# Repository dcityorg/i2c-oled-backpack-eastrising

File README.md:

#### I²C OLED Backpack Board for the East Rising OLED display (2 rows by 16 characters)

<div style="text-align: center;">
<div style="display: inline-block; margin-right: 5px;">

</div>
<div style="display: inline-block; margin-right: 5px;">

</div>
<div style="display: inline-block; margin-right: 5px;">

</div>
</div>

Introduction
-------------------

**[This link has details](https://www.dcity.org/portfolio/i2c-oled-backpack-board-eastrising) including**
* parts lists
* assembly instructions
* jumper configuration
* Arduino, Particle and Raspberry Pi software library usage
* Bare PC boards are available from OSHPark.

**License Information**
Open Source Hardware Design. Our License Information is [here](https://www.dcity.org/license-information/).

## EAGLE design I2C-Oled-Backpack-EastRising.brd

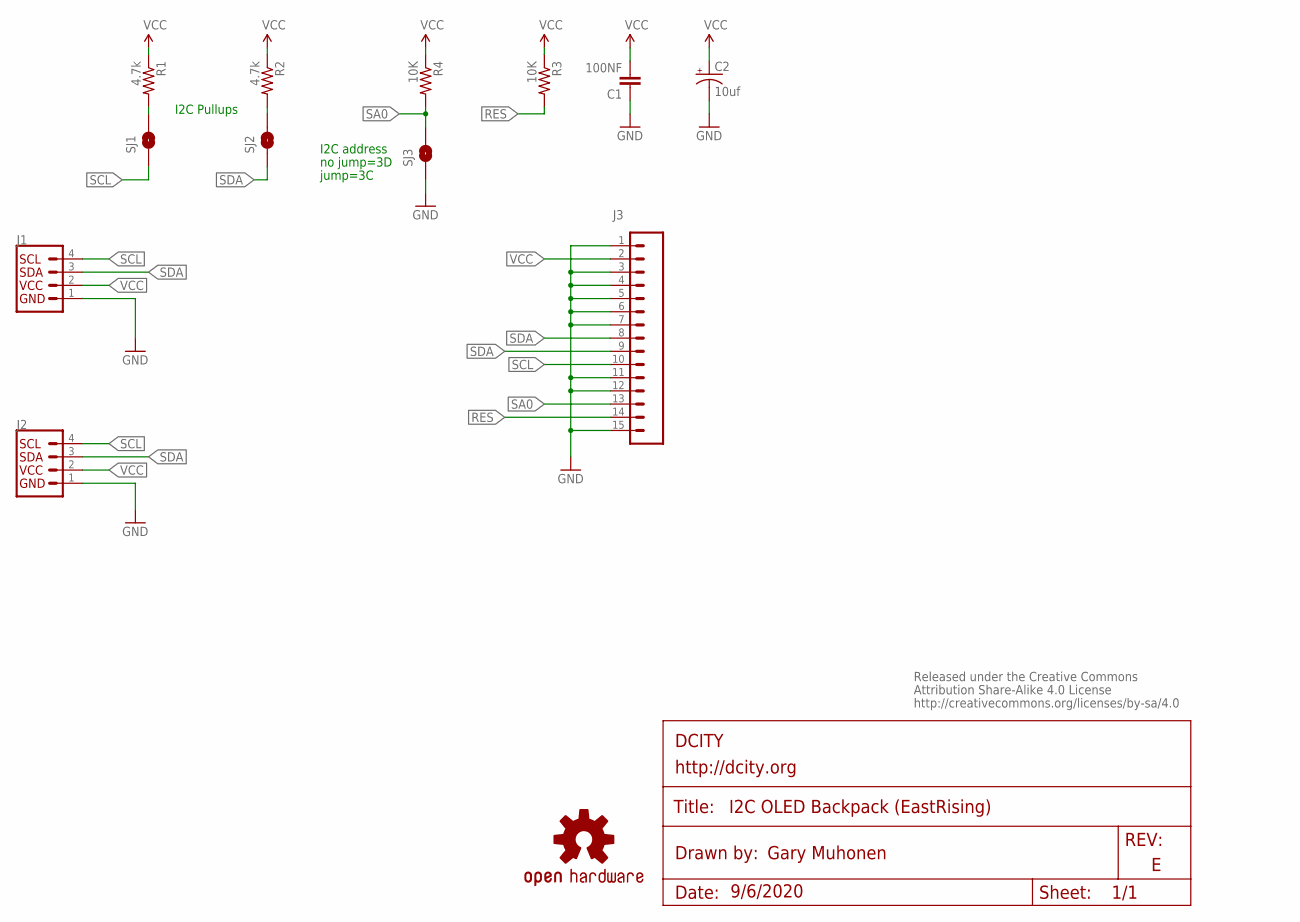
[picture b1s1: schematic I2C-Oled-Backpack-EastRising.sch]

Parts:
C1: 100NF; 0805-CAP
C2: 10uf; 0805-POL
J1, J2: QWIIC_RIGHT_ANGLE; JST04_1MM_RA
J3: 15P-2.54; 1X15_LOCK
LOGO1: OSHW-LOGOS; OSHW-LOGO-S
R1, R2: 4.7k; 0805-RES
R3, R4: 10K; 0805-RES
SJ1, SJ2, SJ3: SOLDERJUMPERNC; SJ_2S
U$2: CREATIVE_COMMONS

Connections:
GND: C1.1, C2.-, J1.1, J2.1, J3.1, J3.3, J3.4, J3.5, J3.6, J3.7, J3.11, J3.12, J3.15, SJ3.1
unnamed: R1.2, SJ1.2
unnamed: R2.2, SJ2.2
RES: J3.14, R3.2
SA0: J3.13, R4.2, SJ3.2
SCL: J1.4, J2.4, J3.10, SJ1.1
SDA: J1.3, J2.3, J3.8, J3.9, SJ2.1
VCC: C1.2, C2.+, J1.2, J2.2, J3.2, R1.1, R2.1, R3.1, R4.1

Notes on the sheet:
I2C address
no jump=3D
jump=3C
I2C Pullups

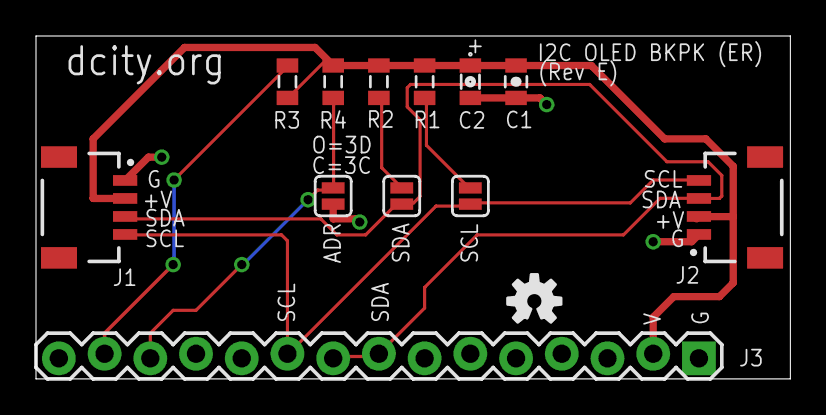
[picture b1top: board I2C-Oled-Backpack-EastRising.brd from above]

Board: 2 copper layers, 41.9 x 19.1 mm, 14 parts (0 on the bottom side), 8 nets.

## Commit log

2016-03-31 First commit - Rev C
2016-03-31 minor changes to readme.md
2016-04-13 changed pictures in readme.md
2018-09-14 Rev D
2020-10-11 Rev E

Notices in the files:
parts and their libraries:
0: Released under the Creative Commons
0: http://creativecommons.org/licenses/by-sa/4.0
